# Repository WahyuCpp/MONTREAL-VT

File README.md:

File Terbaru ada di folder current_progress.

Folder lainnya cuma backup.

Git pull di lokal, atau download zip buat recompile mandiri.

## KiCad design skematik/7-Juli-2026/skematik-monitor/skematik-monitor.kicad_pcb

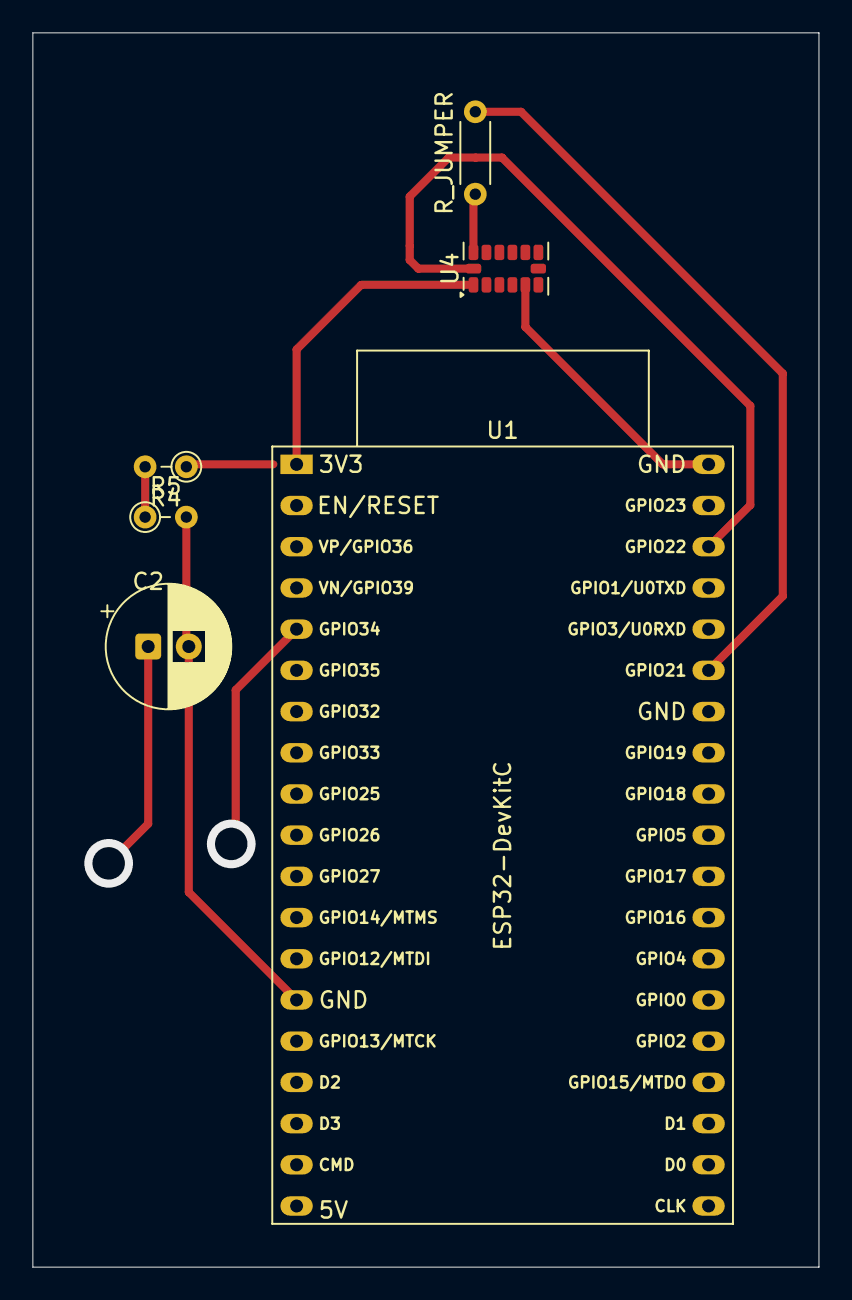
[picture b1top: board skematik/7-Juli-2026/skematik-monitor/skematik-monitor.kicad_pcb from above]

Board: 2 copper layers, 48.5 x 76.1 mm, 6 parts (0 on the bottom side), 5 nets.

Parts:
C2: 10n; CP_Radial_D7.5mm_P2.50mm
R4: 880; R_Axial_DIN0204_L3.6mm_D1.6mm_P2.54mm_Vertical
R5: 330; R_Axial_DIN0204_L3.6mm_D1.6mm_P2.54mm_Vertical
R_JUMPER: R_Axial_DIN0204_L3.6mm_D1.6mm_P5.08mm_Horizontal
U1: ESP32-DevKitC
U4: ADXL345; LGA-14_3x5mm_P0.8mm_LayoutBorder1x6y

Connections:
3V3: R4.1, U1.1 (3V3), U4.1 (Vdd_I/O)
GND: C2.2, R5.2, U1.14 (GND), U1.32 (GND), U1.38 (GND), U4.2 (GND), U4.4 (GND), U4.5 (GND)
unnamed: C2.1, R4.2, R5.1
SCL: U1.36 (GPIO22), U4.14 (SCL/SCLK)
SDA: R_JUMPER.1, R_JUMPER.2, U1.33 (GPIO21), U4.13 (SDA/SDI/SDIO)

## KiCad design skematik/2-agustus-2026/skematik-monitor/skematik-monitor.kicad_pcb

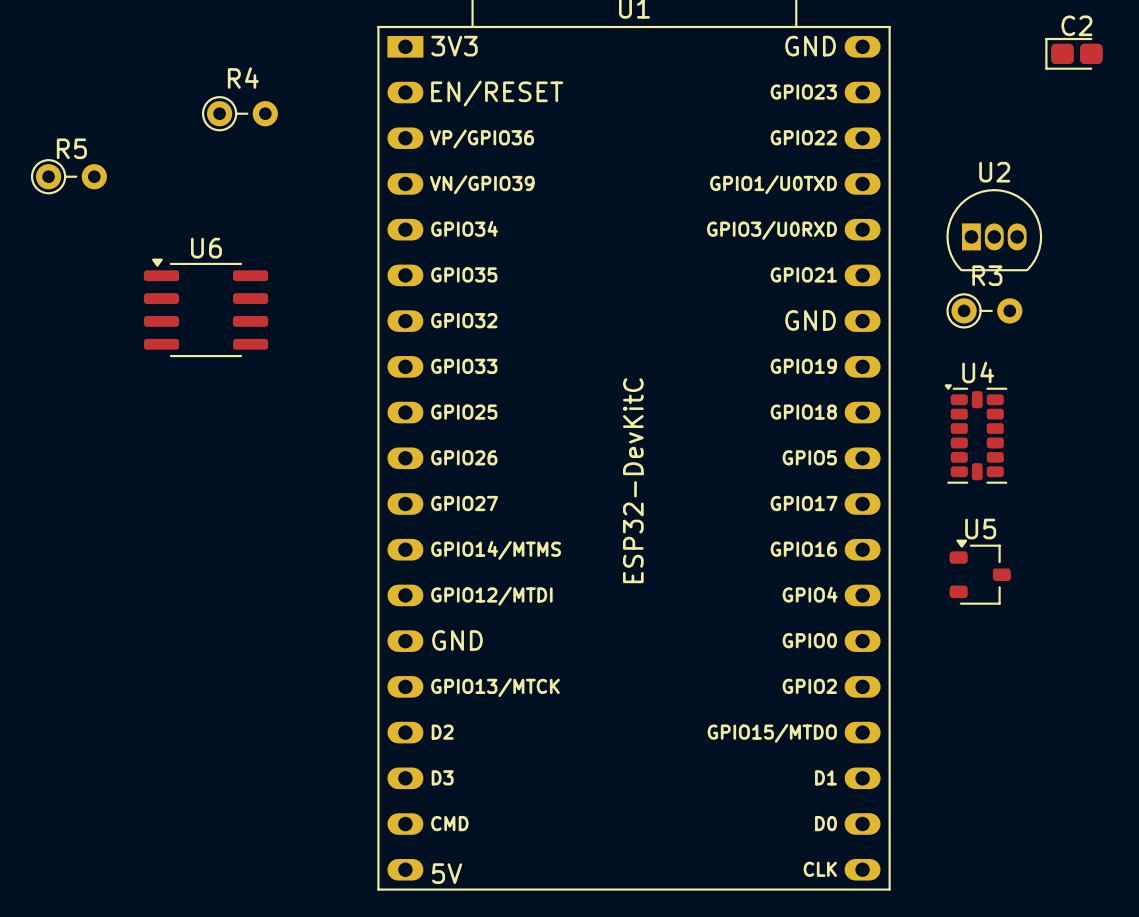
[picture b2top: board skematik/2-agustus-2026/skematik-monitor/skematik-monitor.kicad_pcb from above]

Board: 2 copper layers, 9 parts (0 on the bottom side), 10 nets, no tracks yet.

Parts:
C2: 100n; CP_EIA-1608-08_AVX-J_HandSolder
R3, R5: 3.3k; R_Axial_DIN0204_L3.6mm_D1.6mm_P2.54mm_Vertical
R4: 330; R_Axial_DIN0204_L3.6mm_D1.6mm_P2.54mm_Vertical
U1: ESP32-DevKitC
U2: DS18B20; TO-92_Inline
U4: ADXL345; LGA-14_3x5mm_P0.8mm_LayoutBorder1x6y
U5: A3104xLH; SOT-23W
U6: ACS712xLCTR-05B; SOIC-8_3.9x4.9mm_P1.27mm

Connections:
3V3: R3.1, U1.1 (3V3), U2.3 (V_{DD}), U4.1 (Vdd_I/O), U5.1 (V_{CC}), U6.8 (VCC)
/Current Sensor A/GPIO34: R4.2, R5.2, U1.5 (VDET_1/GPIO34/ADC1_CH6)
GND: C2.2, R5.1, U1.14 (GND), U1.32 (GND), U1.38 (GND), U2.1 (GND), U4.2 (GND), U4.4 (GND), U4.5 (GND), U5.3 (GND), U6.3 (IP-), U6.4 (IP-), U6.5 (GND)
GPIO35: R3.2, U1.6 (VDET_2/GPIO35/ADC1_CH7), U2.2 (DQ)
GPIO36: U1.3 (SENSOR_VP/GPIO36/ADC1_CH0), U5.2 (V_{OUT})
unnamed: U6.1 (IP+), U6.2 (IP+)
unnamed: C2.1, U6.6 (FILTER)
unnamed: R4.1, U6.7 (VIOUT)
SCL: U1.36 (GPIO22), U4.14 (SCL/SCLK)
SDA: U1.33 (GPIO21), U4.13 (SDA/SDI/SDIO)
